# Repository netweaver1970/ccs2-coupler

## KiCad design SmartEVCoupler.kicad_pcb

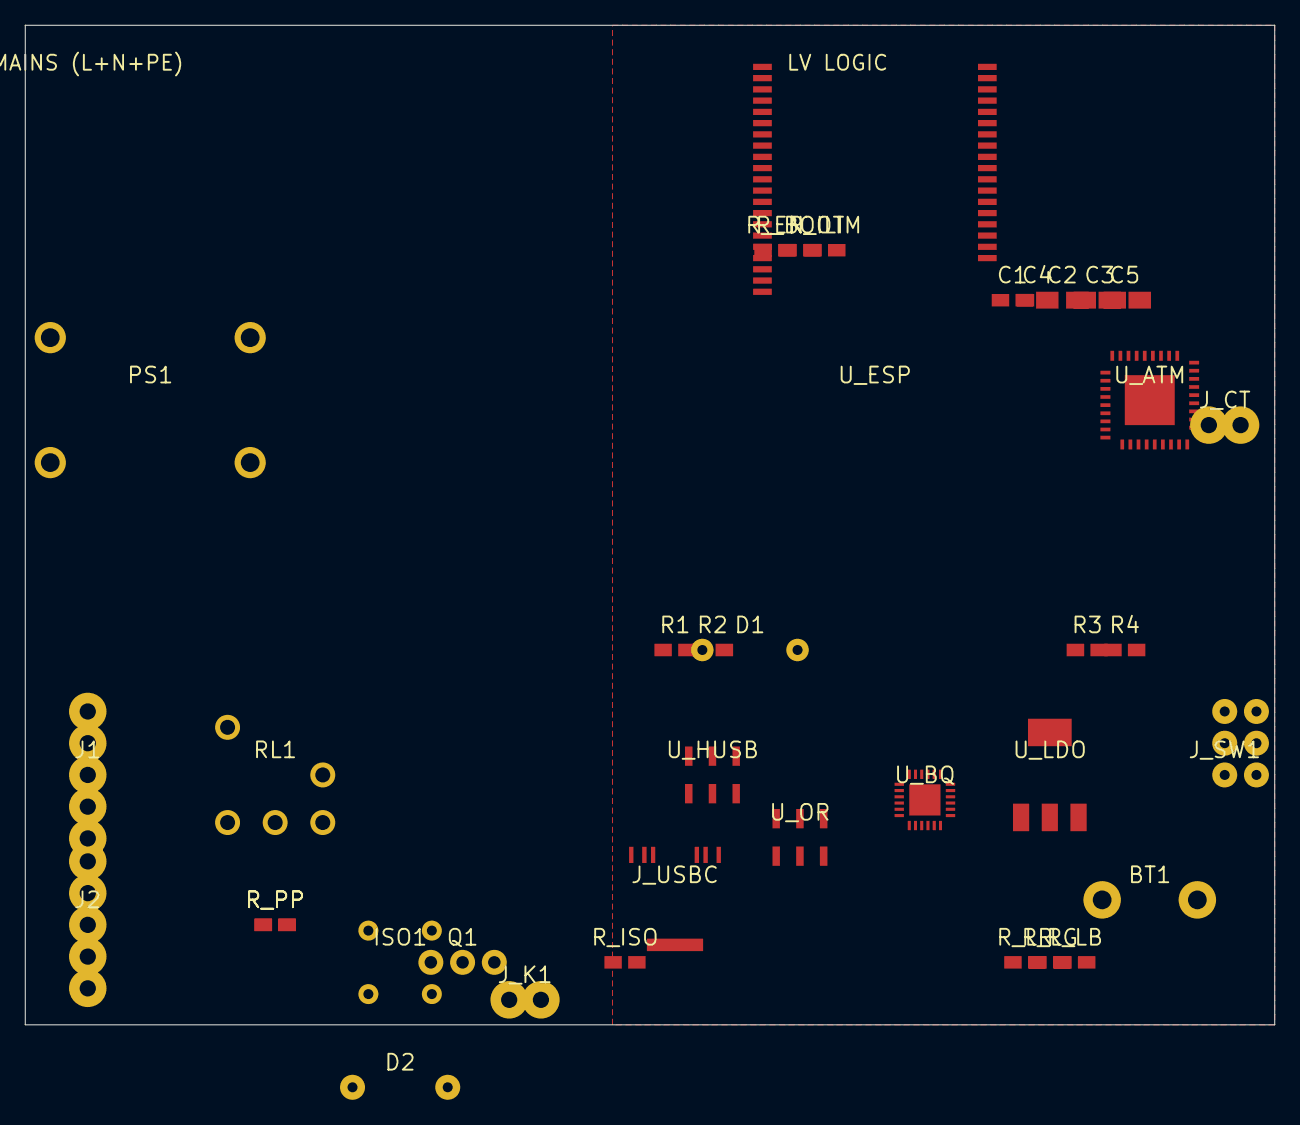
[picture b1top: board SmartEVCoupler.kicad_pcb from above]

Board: 2 copper layers, 100.0 x 80.0 mm, 37 parts (0 on the bottom side), 28 nets, no tracks yet.

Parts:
BT1: 18650; Battery18650
C1, C4: 100nF; R_0402
C2, C3, C5: 10µF; C_0805
D1: BZX55C3V3
D2: 1N4007
ISO1: PC817C
J1: Type2-Wallbox-IN; KF301-5P
J2: Type2-Car-OUT; KF301-5P
J_CT: SCT-013-030 CT; KF301-2P
J_K1: Contactor-Coil; KF301-2P
J_SW1: SW1 Button; PinHeader_2x3
J_USBC: USB-C 16P; USBC-16P
PS1: HLK-5M05
Q1: IRLZ44NPBF
R1: 100kΩ; R_0402
R2: 47kΩ; R_0402
R3, R4: 470kΩ; R_0402
RL1: SRD-05VDC-SL-C
R_BOOT: 10kΩ; R_0402
R_EN: 10kΩ; R_0402
R_ILIM: 10kΩ; R_0402
R_ISO: 100Ω; R_0402
R_LB: 33Ω; R_0402
R_LG: 33Ω; R_0402
R_LR: 33Ω; R_0402
R_PP: 2.7kΩ; R_0402
R_PP#2: 2.7kΩ; R_0402
U_ATM: ATM90E32AS
U_BQ: BQ25895RTWT
U_ESP: ESP32-S3-WROOM-1-N16R8; ESP32-S3-WROOM-1
U_HUSB: HUSB238_002D
U_LDO: AMS1117-3.3
U_OR: LTC4413

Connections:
AC_L: J1.3, PS1.1, R3.1
AC_N: J1.2, J2.2, PS1.2
ATM_VA_MID: R3.2, R4.1
BAT_P: BT1.1, C5.1
CC1: J_USBC.A5, U_HUSB.3
CC2: J_USBC.B5, U_HUSB.5
CP_IN: J1.4, R1.1, RL1.3
CP_MID: D1.2, R1.2, R2.1
CP_OUT: J2.4, RL1.4
EN: R_EN.2, U_ESP.3, U_OR.3
GND: BT1.2, C1.2, C2.2, C3.2, C4.2, C5.2, D1.1, D2.1, ISO1.2, ISO1.3, J_K1.2, J_SW1.2, J_SW1.6, J_USBC.A1, J_USBC.B1, J_USBC.S1, PS1.4, Q1.3, R2.2, R4.2, RL1.2, R_ILIM.2, R_PP.2, R_PP#2.2, U_ATM.37, U_BQ.25, U_ESP.1, U_HUSB.2, U_LDO.1, U_OR.1
IO0_BOOT: R_BOOT.2, U_ESP.27
K1_A1: D2.2, J_K1.1, Q1.2
K1_DRV: R_ISO.1, U_ESP.5
K1_DRV_A: ISO1.1, R_ISO.2
K1_GATE_N: ISO1.4, Q1.1
LED_BO: J_SW1.5, R_LB.2
LED_B_IO: R_LB.1, U_ESP.21
LED_GO: J_SW1.4, R_LG.2
LED_G_IO: R_LG.1, U_ESP.20
LED_RO: J_SW1.3, R_LR.2
LED_R_IO: R_LR.1, U_ESP.7
PE: J1.1, J2.1
PP_NET: J1.5, J2.5, R_PP.1, R_PP#2.1
RL1_COIL: RL1.1, U_ESP.4
VBUS_USB: J_USBC.A4, J_USBC.A4b
VCC33: C1.1, C2.1, R_BOOT.1, R_EN.1, U_ESP.2, U_LDO.2, U_LDO.4
VSYS: C3.1, C4.1, U_LDO.3

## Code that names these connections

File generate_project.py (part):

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
# HLK-5M05  PS1
SCH_ITEMS.append(sch_sym("HLK-5M05","PS1","HLK-5M05","evc:HLK-5M05",
    30,165, pin_nets={"1":"AC_L","2":"AC_N","3":"VBUS_HLK","4":"GND"}))
SCH_ITEMS.append(label("AC_L",      17.62, 165))
SCH_ITEMS.append(label("AC_N",      17.62, 167.54))
SCH_ITEMS.append(label("VBUS_HLK", 42.62+G, 165))

# J_USBC  USB-C 16P
SCH_ITEMS.append(sch_sym("USBC-16P","J_USBC","USB-C 16P","evc:USBC-16P",
    30,195, pin_nets={"A1":"GND","A4":"VBUS_USB","A5":"CC1","B5":"CC2",
                      "S1":"GND","A6":"NC","A7":"NC","B6":"NC","B7":"NC"}))
SCH_ITEMS.append(label("VBUS_USB", 42.62+G, 192.46))
SCH_ITEMS.append(label("CC1",      42.62+G, 189.92))
SCH_ITEMS.append(label("CC2",      42.62+G, 187.38))
SCH_ITEMS += [nc(42.62+G, 184.84), nc(42.62+G, 182.3), nc(42.62+G, 179.76), nc(42.62+G, 177.22)]
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                      "1":"VBUS_USB","6":"GND","7":"GND","8":"GND","9":"NC"}))
SCH_ITEMS.append(label("CC1",     62.38-G, 192.46))
SCH_ITEMS.append(label("CC2",     62.38-G, 189.92))
SCH_ITEMS.append(label("VBUS_USB",62.38-G, 195))
SCH_ITEMS.append(nc(87.62+G, 192.46))

# U_OR  LTC4413
SCH_ITEMS.append(sch_sym("LTC4413","U_OR","LTC4413","evc:LTC4413",
    115,180, pin_nets={"2":"VBUS_USB","6":"VBUS_HLK","1":"GND",
                       "4":"VBUS_IN","5":"VBUS_IN","3":"VCC33"}))
SCH_ITEMS.append(label("VBUS_USB", 102.38-G, 177.46))
SCH_ITEMS.append(label("VBUS_HLK", 102.38-G, 172.38))
SCH_ITEMS.append(label("VBUS_IN",  127.62+G, 177.46))

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        "18":"NC","19":"I2C_SDA","20":"I2C_SCL",
        "21":"GND","5":"NC"}))
SCH_ITEMS.append(label("VBUS_IN",  147.38-G, 192.46))
SCH_ITEMS.append(label("VSYS",     172.62+G, 192.46))
SCH_ITEMS.append(label("BAT_P",    147.38-G, 189.92))
SCH_ITEMS.append(label("QON",      172.62+G, 187.38))
SCH_ITEMS.append(label("BQ_INT",   172.62+G, 184.84))
SCH_ITEMS.append(label("I2C_SDA",  172.62+G, 182.3))
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
# U_LDO  AMS1117-3.3
SCH_ITEMS.append(sch_sym("AMS1117-3.3","U_LDO","AMS1117-3.3","evc:AMS1117-3.3",
    195,195, pin_nets={"3":"VSYS","2":"VCC33","4":"VCC33","1":"GND"}))
SCH_ITEMS.append(label("VSYS",  182.38-G, 195))
SCH_ITEMS.append(label("VCC33", 207.62+G, 195))

# BT1  18650 holder
SCH_ITEMS.append(sch_sym("Battery18650","BT1","18650","evc:Battery18650",
    150,225, pin_nets={"1":"BAT_P","2":"GND"}))
SCH_ITEMS.append(label("BAT_P", 137.38-G, 225))

# Decoupling caps
SCH_ITEMS.append(sch_sym("C_100n","C1","100nF","evc:C_0402", 205,215,
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SCH_ITEMS.append(sch_sym("C_10u_0805","C2","10µF","evc:C_0805", 212,215,
    pin_nets={"1":"VCC33","2":"GND"}))
SCH_ITEMS.append(sch_sym("C_100n","C4","100nF","evc:C_0402", 219,215,
    pin_nets={"1":"VSYS","2":"GND"}))
SCH_ITEMS.append(sch_sym("C_10u_0805","C3","10µF","evc:C_0805", 226,215,
    pin_nets={"1":"VSYS","2":"GND"}))
SCH_ITEMS.append(sch_sym("C_10u_0805","C5","10µF","evc:C_0805", 160,240,
    pin_nets={"1":"BAT_P","2":"GND"}))
for net in ["VCC33","VCC33","VSYS","VSYS","BAT_P"]:
    pass  # labels already implied by pin_nets above

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
# J1  Type 2 input (wallbox side)
SCH_ITEMS.append(sch_sym("KF301-5P","J1","Type2-Wallbox-IN","evc:KF301-5P",
    25,60, pin_nets={"1":"PE","2":"AC_N","3":"AC_L","4":"CP_IN","5":"PP_NET"}))
SCH_ITEMS.append(label("PE",     12.38-G, 62.54))
SCH_ITEMS.append(label("AC_N",   12.38-G, 60))
SCH_ITEMS.append(label("AC_L",   12.38-G, 57.46))
SCH_ITEMS.append(label("CP_IN",  12.38-G, 54.92))
SCH_ITEMS.append(label("PP_NET", 12.38-G, 52.38))

# J2  Type 2 output (car side)
SCH_ITEMS.append(sch_sym("KF301-5P","J2","Type2-Car-OUT","evc:KF301-5P",
    25,100, pin_nets={"1":"PE","2":"AC_N","3":"AC_L_SW","4":"CP_OUT","5":"PP_NET"}))
SCH_ITEMS.append(label("PE",      12.38-G, 102.54))
SCH_ITEMS.append(label("AC_N",    12.38-G, 100))
SCH_ITEMS.append(label("AC_L_SW", 12.38-G, 97.46))
SCH_ITEMS.append(label("CP_OUT",  12.38-G, 94.92))
SCH_ITEMS.append(label("PP_NET",  12.38-G, 92.38))

# R_PP  2.7kΩ proximity pilot termination
SCH_ITEMS.append(sch_sym("R_2k7","R_PP","2.7kΩ","evc:R_0402",
    50,115, pin_nets={"1":"PP_NET","2":"GND"}))
SCH_ITEMS.append(label("PP_NET", 37.38-G, 115))

# RL1  SRD-05VDC relay (CP interlock — NC = fail-safe)
SCH_ITEMS.append(sch_sym("SRD-05VDC-SL-C","RL1","SRD-05VDC-SL-C","evc:SRD-05VDC-SL-C",
    80,60, pin_nets={"1":"RL1_COIL","2":"GND","3":"CP_IN","4":"CP_OUT","5":"NC_RL1"}))
SCH_ITEMS.append(label("RL1_COIL", 67.38-G, 61.27))
SCH_ITEMS.append(label("CP_IN",    92.62+G, 61.27))
SCH_ITEMS.append(label("CP_OUT",   92.62+G, 60))
SCH_ITEMS.append(nc(92.62+G, 58.73))

# CP voltage divider + ADC clamp
# R1 100kΩ: CP_IN → CP_MID
SCH_ITEMS.append(sch_sym("R_100k","R1","100kΩ","evc:R_0402",
    120,55, pin_nets={"1":"CP_IN","2":"CP_MID"}))
SCH_ITEMS.append(label("CP_IN",  107.38-G, 55))
SCH_ITEMS.append(label("CP_MID", 132.62+G, 55))
# R2 47kΩ: CP_MID → GND
SCH_ITEMS.append(sch_sym("R_47k","R2","47kΩ","evc:R_0402",
    140,55, pin_nets={"1":"CP_MID","2":"GND"}))
SCH_ITEMS.append(label("CP_MID", 127.38-G, 55))
# D1 BZX55C3V3: CP_MID → GND (zener clamp)
SCH_ITEMS.append(sch_sym("BZX55C3V3","D1","BZX55C3V3","evc:BZX55C3V3",
    155,55, pin_nets={"1":"GND","2":"CP_MID"}))
SCH_ITEMS.append(label("CP_MID", 162.38+G, 55))
# Label CP_MID → CP_ADC to ESP32
SCH_ITEMS.append(label("CP_ADC", 132.62+G, 57.54))

# ISO1  PC817C optocoupler (K1 gate driver input)
SCH_ITEMS.append(sch_sym("PC817C","ISO1","PC817C","evc:PC817C",
    80,100, pin_nets={"1":"K1_DRV_A","2":"GND","4":"K1_GATE_N","3":"GND"}))
SCH_ITEMS.append(label("K1_DRV_A",  67.38-G, 101.27))
SCH_ITEMS.append(label("K1_GATE_N", 92.62+G, 101.27))

# Q1  IRLZ44N MOSFET
SCH_ITEMS.append(sch_sym("IRLZ44NPBF","Q1","IRLZ44NPBF","evc:IRLZ44NPBF",
    115,100, pin_nets={"1":"K1_GATE_N","2":"K1_A1","3":"GND"}))
SCH_ITEMS.append(label("K1_GATE_N", 102.38-G, 100))
SCH_ITEMS.append(label("K1_A1",     127.62+G, 101.27))

# D2  1N4007 flyback
SCH_ITEMS.append(sch_sym("1N4007","D2","1N4007","evc:1N4007",
    145,100, pin_nets={"1":"GND","2":"K1_A1"}))
SCH_ITEMS.append(label("K1_A1", 152.62+G, 100))

# J_K1  contactor coil terminal
SCH_ITEMS.append(sch_sym("KF301-2P","J_K1","Contactor K1 Coil","evc:KF301-2P",
    175,100, pin_nets={"1":"K1_A1","2":"GND"}))
SCH_ITEMS.append(label("K1_A1", 162.38-G, 100))

# ─── SECTION D — ESP32 + ATM90E32 ────────────────────────────────────────────

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    230,40, pin_nets={"1":"VCC33","2":"EN"}))
SCH_ITEMS.append(label("EN",     230+G, 42.54))
SCH_ITEMS.append(sch_sym("R_10k","R_BOOT","10kΩ","evc:R_0402",
    245,40, pin_nets={"1":"VCC33","2":"IO0_BOOT"}))
SCH_ITEMS.append(label("IO0_BOOT", 245+G, 42.54))

# K1_DRV isolator: ESP IO5 → ISO1 anode via series resistor
SCH_ITEMS.append(sch_sym("R_10k","R_ISO","100Ω","evc:R_0402",
    210,100, pin_nets={"1":"K1_DRV","2":"K1_DRV_A"}))
SCH_ITEMS.append(label("K1_DRV",   197.38-G, 100))
SCH_ITEMS.append(label("K1_DRV_A", 222.62+G, 100))

# RL1 coil drive: ESP IO4 → direct (active-high relay coil via 3V3→coil→GND)
# (RL1 coil is driven directly from IO4 with flyback diode integrated)
SCH_ITEMS.append(label("RL1_COIL", 215, 115))
SCH_ITEMS.append(text("(IO4 drives RL1 coil directly;\n100mA within ESP GPIO spec)", 215, 118, 1.0))

# QON connect to J_SW1
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
# R3, R4 voltage divider AC_L → ATM_VA (470kΩ + 470kΩ)
SCH_ITEMS.append(sch_sym("R_470k","R3","470kΩ","evc:R_0402",
    320,55, pin_nets={"1":"AC_L","2":"ATM_VA_MID"}))
SCH_ITEMS.append(sch_sym("R_470k","R4","470kΩ","evc:R_0402",
    335,55, pin_nets={"1":"ATM_VA_MID","2":"GND"}))
SCH_ITEMS.append(label("AC_L",       307.38-G, 55))
SCH_ITEMS.append(label("ATM_VA_MID", 322.62+G, 55))
SCH_ITEMS.append(label("ATM_VA",     322.62+G, 57.54))
SCH_ITEMS.append(wire(322.62+G, 55, 322.62+G, 57.54))

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
# LED current-limit resistors + J_SW1 header
SCH_ITEMS.append(sch_sym("R_33","R_LR","33Ω","evc:R_0402",
    305,175, pin_nets={"1":"LED_R_IO","2":"LED_RO"}))
SCH_ITEMS.append(sch_sym("R_33","R_LG","33Ω","evc:R_0402",
    305,180, pin_nets={"1":"LED_G_IO","2":"LED_GO"}))
SCH_ITEMS.append(sch_sym("R_33","R_LB","33Ω","evc:R_0402",
    305,185, pin_nets={"1":"LED_B_IO","2":"LED_BO"}))
SCH_ITEMS.append(label("LED_R_IO", 292.38-G, 175))
SCH_ITEMS.append(label("LED_G_IO", 292.38-G, 180))
SCH_ITEMS.append(label("LED_B_IO", 292.38-G, 185))
SCH_ITEMS.append(label("LED_RO",   317.62+G, 175))
SCH_ITEMS.append(label("LED_GO",   317.62+G, 180))
SCH_ITEMS.append(label("LED_BO",   317.62+G, 185))

SCH_ITEMS.append(sch_sym("PinHeader_2x3","J_SW1","SW1 16mm LED Button","evc:PinHeader_2x3",
    355,180, pin_nets={
    "1":"QON","2":"GND","3":"LED_RO","4":"LED_GO","5":"LED_BO","6":"GND"}))
SCH_ITEMS.append(label("QON",    342.38-G, 181.27))
SCH_ITEMS.append(label("LED_RO", 342.38-G, 180))
SCH_ITEMS.append(label("LED_GO", 342.38-G, 178.73))
SCH_ITEMS.append(label("LED_BO", 367.62+G, 181.27))

# I2C connections label
SCH_ITEMS.append(label("I2C_SDA", 215, 155))
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
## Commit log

2026-05-24 Add complete KiCad 8 project for Smart Type 2 AC EV Inline Coupler
    Generates a self-contained KiCad 8 project without EasyEDA API access:
    • lib/evc.kicad_sym — 24-component custom symbol library (ESP32-S3-WROOM-1,
    BQ25895RTWT, HUSB238_002D, LTC4413, AMS1117-3.3, ATM90E32AS, SRD-05VDC,
    PC817C, IRLZ44N, HLK-5M05, Battery18650, USBC-16P, KF301-5P/2P,
    PinHeader_2x3, BZX55C3V3, 1N4007, passives). All LCSC part numbers encoded
    as symbol properties.
2026-05-24 Add real footprints from KiCad/Espressif libs; replace ESP32-S3-WROOM-1 symbol with Espressif official
2026-05-26 Add KiCad 10 native project for Smart Type 2 AC EV Inline Coupler
    Generate all project files with KiCad 10 format version (20250610 / "10.0").
    Includes generator script, schematic, PCB layout, symbol library, BOM,
    footprint/symbol library tables, and project config.
2026-05-26 Hide pin numbers on all symbols to prevent overlap with pin names
    https://claude.ai/code/session_01HtYCFycwjAHofQsQUDsT5P
2026-05-26 Use deterministic UUIDs for PCB zones; regenerate schematic/pcb
    https://claude.ai/code/session_01HtYCFycwjAHofQsQUDsT5P
